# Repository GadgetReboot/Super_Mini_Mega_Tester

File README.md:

# Super_Mini_Mega_Tester
<br><br><BR><BR>
40 Pin Cable Tester platform using ESP32-C3 Super Mini module<BR><BR>
JP1 through JP15 jumpers must have solder jumpers blobbed on to set the addresses of the five GPIO expander ICs.

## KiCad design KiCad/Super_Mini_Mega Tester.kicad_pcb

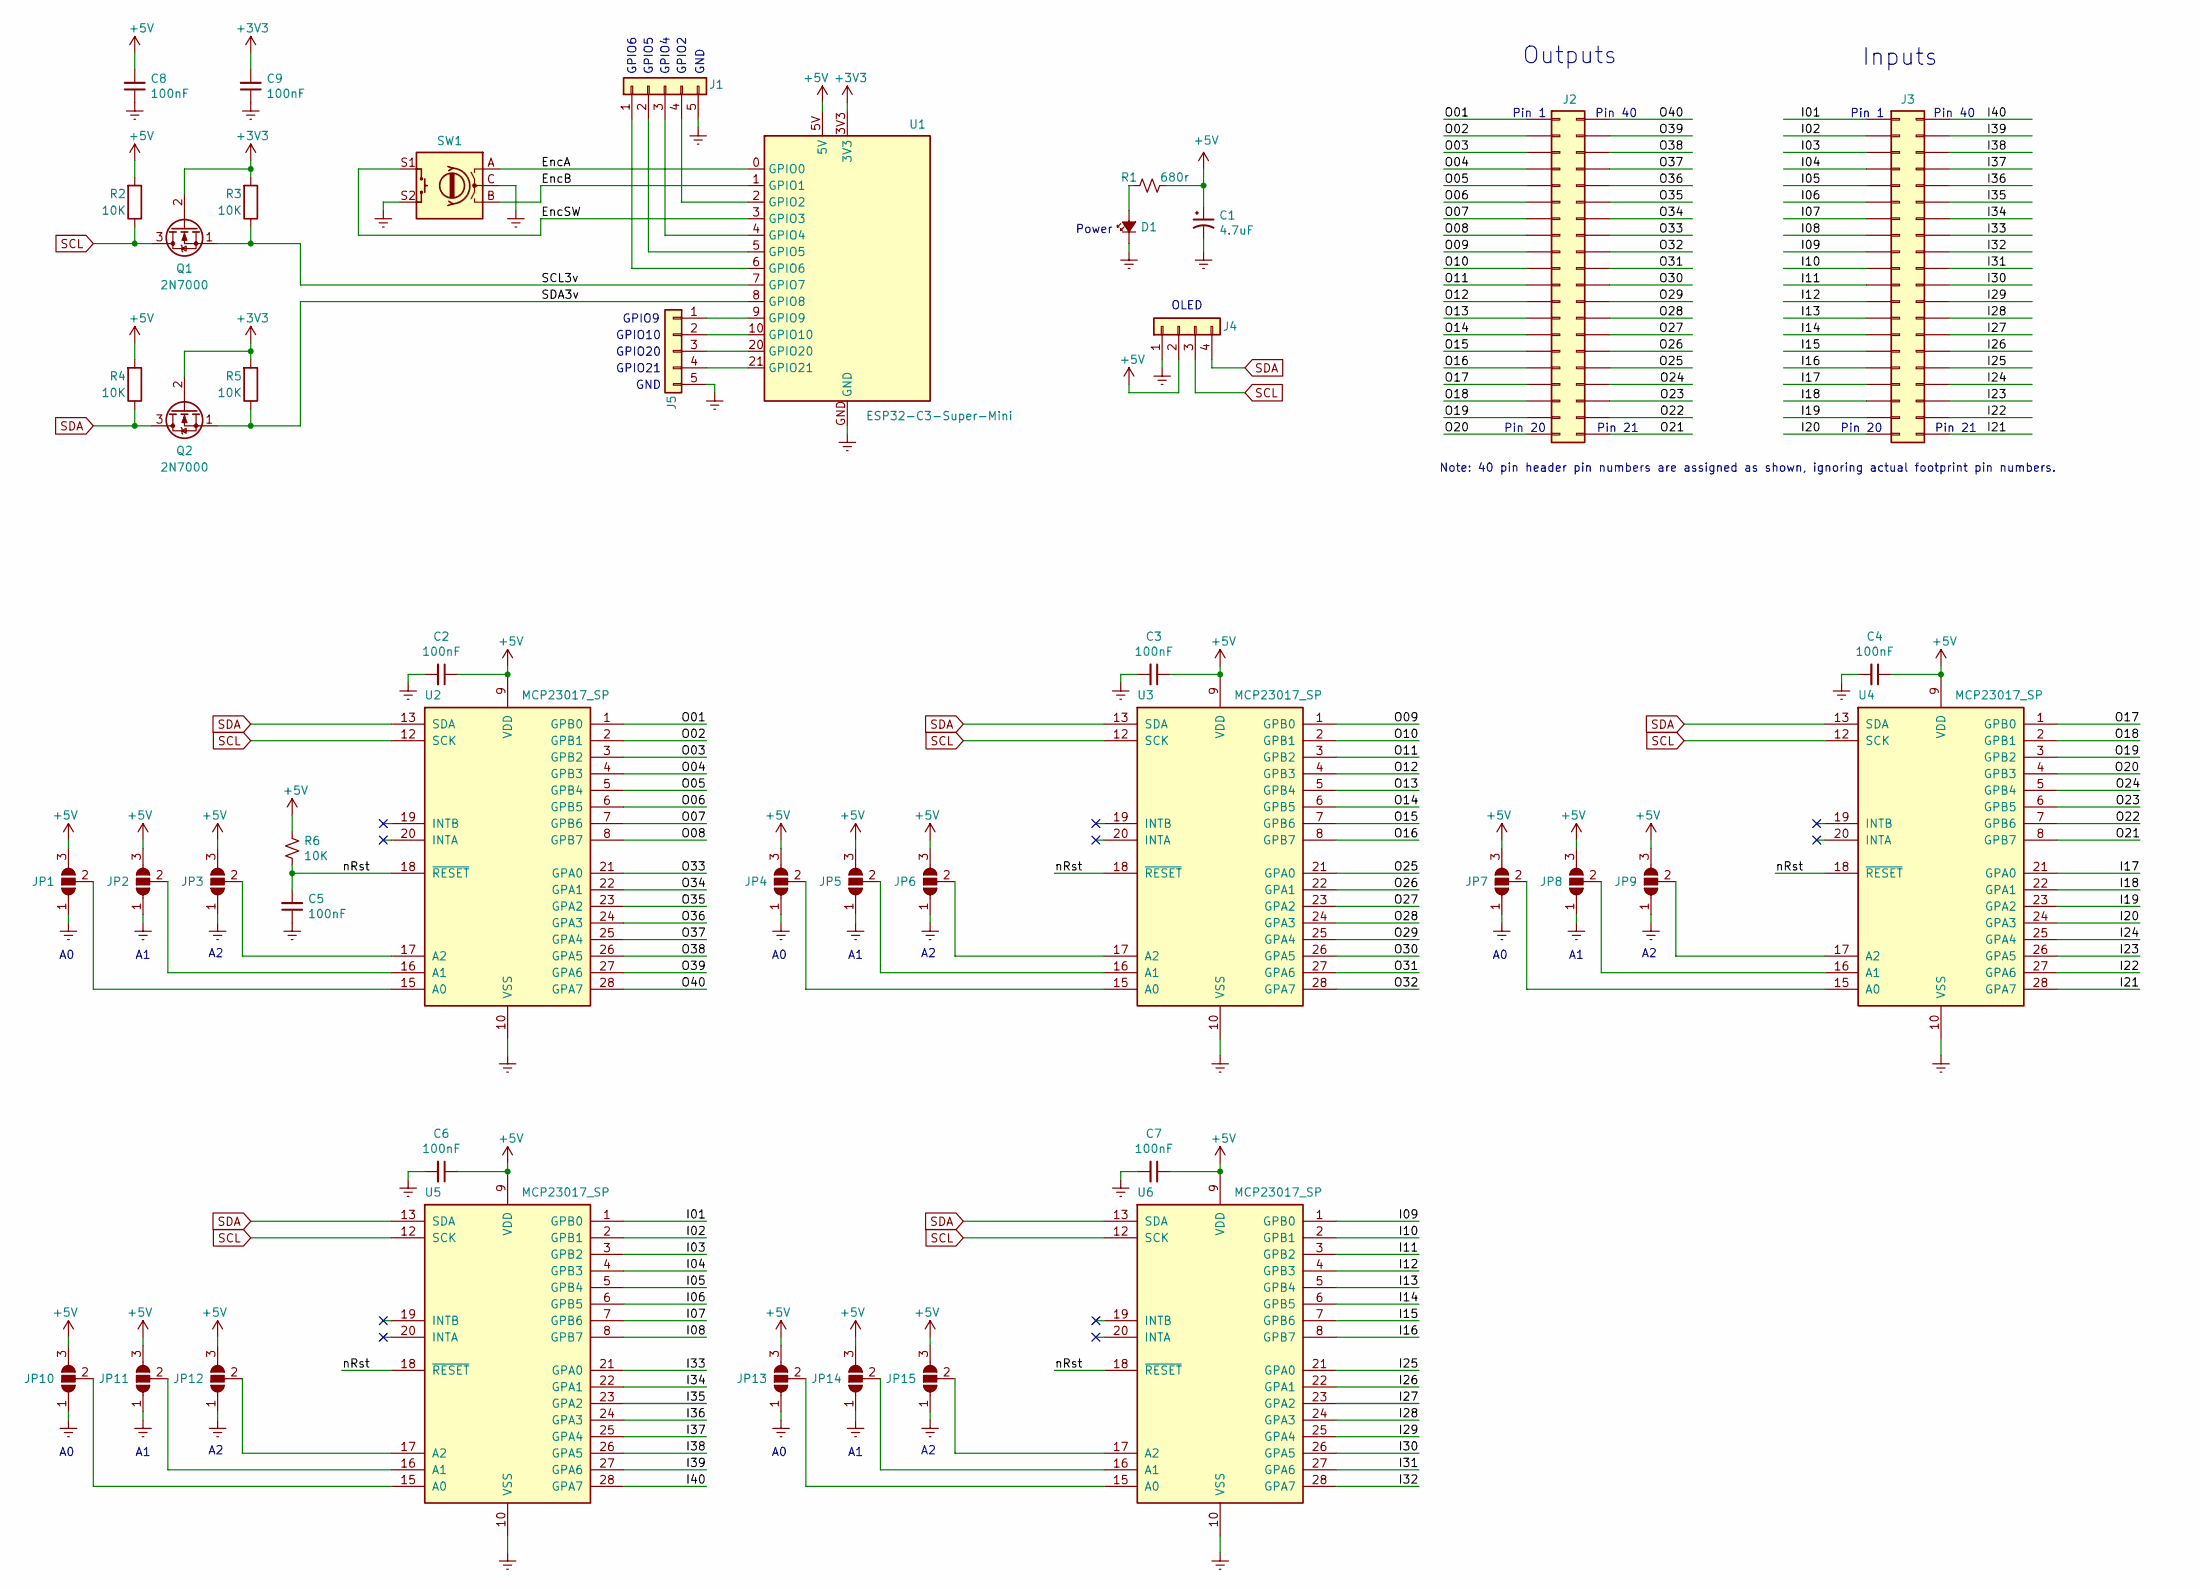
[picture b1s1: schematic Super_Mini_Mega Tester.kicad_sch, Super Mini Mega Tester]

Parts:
C1: 4.7uF; CP_Radial_D5.0mm_P2.50mm
C2, C3, C4, C5, C6, C7, C8, C9: 100nF; C_Disc_D3.8mm_W2.6mm_P2.50mm
D1: LED_Small_ALT; LED_D5.0mm
J1, J5: Conn_01x05; PinHeader_1x05_P2.54mm_Vertical
J2, J3: Conn_02x20_Odd_Even; PinHeader_2x20_P2.54mm_Vertical
J4: Conn_01x04; PinHeader_1x04_P2.54mm_Vertical
JP1, JP2, JP3, JP4, JP5, JP6, JP7, JP8, JP9, JP10, JP11, JP12, JP13, JP14, JP15: SolderJumper_3_Open; SolderJumper-3_P1.3mm_Open_RoundedPad1.0x1.5mm_NumberLabels
Q1, Q2: 2N7000; TO-92_Inline
R1: 680r; R_Axial_DIN0207_L6.3mm_D2.5mm_P10.16mm_Horizontal
R2, R3, R4, R5, R6: 10K; R_Axial_DIN0207_L6.3mm_D2.5mm_P10.16mm_Horizontal
SW1: RotaryEncoder_Switch; RotaryEncoder_Alps_EC11E-Switch_Vertical_H20mm_CircularMoun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
U1: ESP32-C3-Super-Mini; ESP32C3_Super_Mini
U2, U3, U4, U5, U6: MCP23017_SP; DIP-28_W7.62mm

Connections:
+3V3: C9.2, Q1.2 (G), Q2.2 (G), R3.2, R5.2, U1.3V3
+5V: C1.1, C2.1, C3.1, C4.1, C6.1, C7.1, C8.2, J4.2, JP1.3 (B), JP2.3 (B), JP3.3 (B), JP4.3 (B), JP5.3 (B), JP6.3 (B), JP7.3 (B), JP8.3 (B), JP9.3 (B), JP10.3 (B), JP11.3 (B), JP12.3 (B), JP13.3 (B), JP14.3 (B), JP15.3 (B), R1.1, R2.2, R4.2, R6.1, U1.5V, U2.9 (VDD), U3.9 (VDD), U4.9 (VDD), U5.9 (VDD), U6.9 (VDD)
/EncA: SW1.A, U1.0 (GPIO0)
/EncB: SW1.B, U1.1 (GPIO1)
/EncSW: SW1.S1, U1.3 (GPIO3)
/I01: J3.1, U5.1 (GPB0)
/I02: J3.3, U5.2 (GPB1)
/I03: J3.5, U5.3 (GPB2)
/I04: J3.7, U5.4 (GPB3)
/I05: J3.9, U5.5 (GPB4)
/I06: J3.11, U5.6 (GPB5)
/I07: J3.13, U5.7 (GPB6)
/I08: J3.15, U5.8 (GPB7)
/I09: J3.17, U6.1 (GPB0)
/I10: J3.19, U6.2 (GPB1)
/I11: J3.21, U6.3 (GPB2)
/I12: J3.23, U6.4 (GPB3)
/I13: J3.25, U6.5 (GPB4)
/I14: J3.27, U6.6 (GPB5)
/I15: J3.29, U6.7 (GPB6)
/I16: J3.31, U6.8 (GPB7)
/I17: J3.33, U4.21 (GPA0)
/I18: J3.35, U4.22 (GPA1)
/I19: J3.37, U4.23 (GPA2)
/I20: J3.39, U4.24 (GPA3)
/I21: J3.40, U4.28 (GPA7)
/I22: J3.38, U4.27 (GPA6)
/I23: J3.36, U4.26 (GPA5)
/I24: J3.34, U4.25 (GPA4)
/I25: J3.32, U6.21 (GPA0)
/I26: J3.30, U6.22 (GPA1)
/I27: J3.28, U6.23 (GPA2)
/I28: J3.26, U6.24 (GPA3)
/I29: J3.24, U6.25 (GPA4)
/I30: J3.22, U6.26 (GPA5)
/I31: J3.20, U6.27 (GPA6)
/I32: J3.18, U6.28 (GPA7)
/I33: J3.16, U5.21 (GPA0)
/I34: J3.14, U5.22 (GPA1)
/I35: J3.12, U5.23 (GPA2)
/I36: J3.10, U5.24 (GPA3)
/I37: J3.8, U5.25 (GPA4)
/I38: J3.6, U5.26 (GPA5)
/I39: J3.4, U5.27 (GPA6)
/I40: J3.2, U5.28 (GPA7)
/O01: J2.1, U2.1 (GPB0)
/O02: J2.3, U2.2 (GPB1)
/O03: J2.5, U2.3 (GPB2)
/O04: J2.7, U2.4 (GPB3)
/O05: J2.9, U2.5 (GPB4)
/O06: J2.11, U2.6 (GPB5)
/O07: J2.13, U2.7 (GPB6)
/O08: J2.15, U2.8 (GPB7)
/O09: J2.17, U3.1 (GPB0)
/O10: J2.19, U3.2 (GPB1)
/O11: J2.21, U3.3 (GPB2)
/O12: J2.23, U3.4 (GPB3)
/O13: J2.25, U3.5 (GPB4)
/O14: J2.27, U3.6 (GPB5)
/O15: J2.29, U3.7 (GPB6)
/O16: J2.31, U3.8 (GPB7)
/O17: J2.33, U4.1 (GPB0)
/O18: J2.35, U4.2 (GPB1)
/O19: J2.37, U4.3 (GPB2)
/O20: J2.39, U4.4 (GPB3)
/O21: J2.40, U4.8 (GPB7)
/O22: J2.38, U4.7 (GPB6)
/O23: J2.36, U4.6 (GPB5)
/O24: J2.34, U4.5 (GPB4)
/O25: J2.32, U3.21 (GPA0)
/O26: J2.30, U3.22 (GPA1)
/O27: J2.28, U3.23 (GPA2)
/O28: J2.26, U3.24 (GPA3)
/O29: J2.24, U3.25 (GPA4)
/O30: J2.22, U3.26 (GPA5)
/O31: J2.20, U3.27 (GPA6)
/O32: J2.18, U3.28 (GPA7)
/O33: J2.16, U2.21 (GPA0)
/O34: J2.14, U2.22 (GPA1)
/O35: J2.12, U2.23 (GPA2)
/O36: J2.10, U2.24 (GPA3)
/O37: J2.8, U2.25 (GPA4)
/O38: J2.6, U2.26 (GPA5)
/O39: J2.4, U2.27 (GPA6)
/O40: J2.2, U2.28 (GPA7)
/SCL3v: Q1.1 (S), R3.1, U1.7 (GPIO7)
/SDA3v: Q2.1 (S), R5.1, U1.8 (GPIO8)
/nRst: C5.2, R6.2, U2.18 (~RESET), U3.18 (~RESET), U4.18 (~RESET), U5.18 (~RESET), U6.18 (~RESET)
GNDREF: C1.2, C2.2, C3.2, C4.2, C5.1, C6.2, C7.2, C8.1, C9.1, D1.1 (K), J1.5, J4.1, J5.5, JP1.1 (A), JP2.1 (A), JP3.1 (A), JP4.1 (A), JP5.1 (A), JP6.1 (A), JP7.1 (A), JP8.1 (A), JP9.1 (A), JP10.1 (A), JP11.1 (A), JP12.1 (A), JP13.1 (A), JP14.1 (A), JP15.1 (A), SW1.C, SW1.S2, U1.GND, U2.10 (VSS), U3.10 (VSS), U4.10 (VSS), U5.10 (VSS), U6.10 (VSS)
unnamed: D1.2 (A), R1.2
unnamed: J1.1, U1.6 (GPIO6)
unnamed: J1.2, U1.5 (GPIO5)
unnamed: J1.3, U1.4 (GPIO4)
unnamed: J1.4, U1.2 (GPIO2)
unnamed: J5.1, U1.9 (GPIO9)
unnamed: J5.2, U1.10 (GPIO10)
unnamed: J5.3, U1.20 (GPIO20)
unnamed: J5.4, U1.21 (GPIO21)
unnamed: JP1.2 (C), U2.15 (A0)
unnamed: JP2.2 (C), U2.16 (A1)
unnamed: JP3.2 (C), U2.17 (A2)
unnamed: JP4.2 (C), U3.15 (A0)
unnamed: JP5.2 (C), U3.16 (A1)
unnamed: JP6.2 (C), U3.17 (A2)
unnamed: JP7.2 (C), U4.15 (A0)
unnamed: JP8.2 (C), U4.16 (A1)
unnamed: JP9.2 (C), U4.17 (A2)
unnamed: JP10.2 (C), U5.15 (A0)
unnamed: JP11.2 (C), U5.16 (A1)
unnamed: JP12.2 (C), U5.17 (A2)
unnamed: JP13.2 (C), U6.15 (A0)
unnamed: JP14.2 (C), U6.16 (A1)
unnamed: JP15.2 (C), U6.17 (A2)
SCL: J4.3, Q1.3 (D), R2.1, U2.12 (SCK), U3.12 (SCK), U4.12 (SCK), U5.12 (SCK), U6.12 (SCK)
SDA: J4.4, Q2.3 (D), R4.1, U2.13 (SDA), U3.13 (SDA), U4.13 (SDA), U5.13 (SDA), U6.13 (SDA)

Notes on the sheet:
OLED
GPIO4
GND
Pin 20
GPIO21
Pin 21
GPIO9
GPIO10
Pin 40
Note: 40 pin header pin numbers are assigned as shown, ignoring actual footprint pin numbers.
GPIO6
Inputs
GPIO5
Pin 1
GPIO2
Power
GPIO20
Outputs

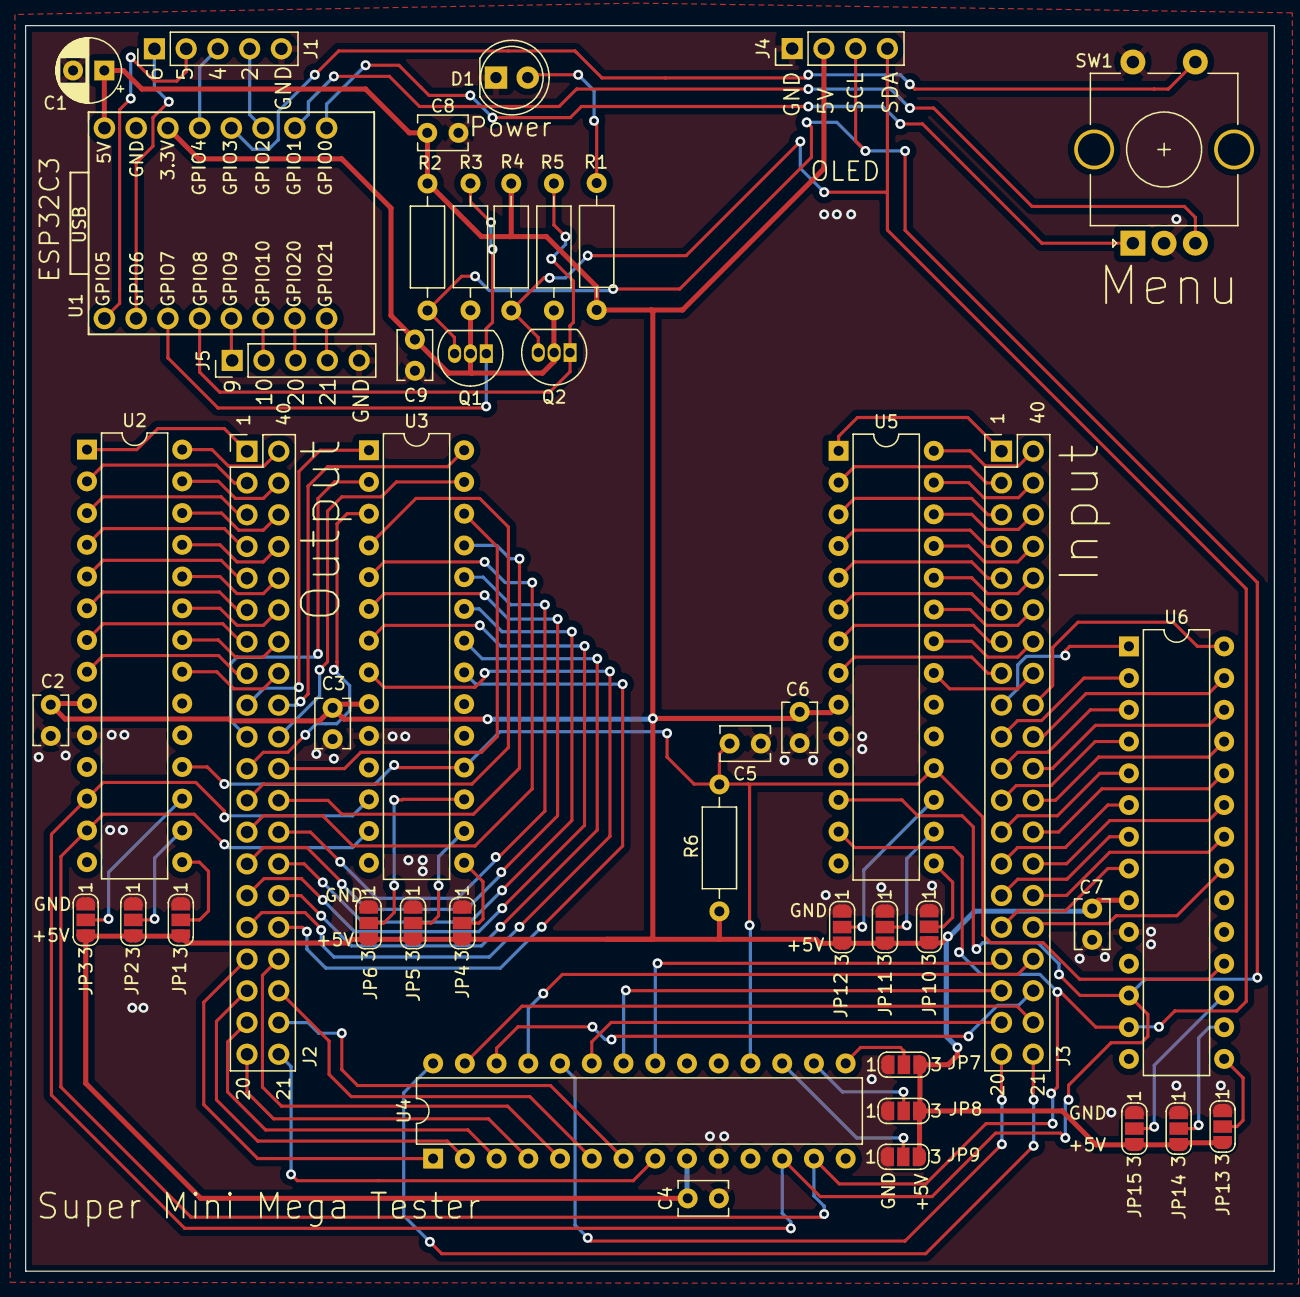
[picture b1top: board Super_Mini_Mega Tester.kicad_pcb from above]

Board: 2 copper layers, 99.9 x 99.7 mm, 45 parts (0 on the bottom side), 115 nets.
